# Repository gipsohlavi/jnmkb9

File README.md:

サリチル酸（https://salicylic-acid3.hatenablog.com/about）  氏の著作「自作キーボード設計ガイド」をもとに作成した、<br>完全自作９キーキーボードです。

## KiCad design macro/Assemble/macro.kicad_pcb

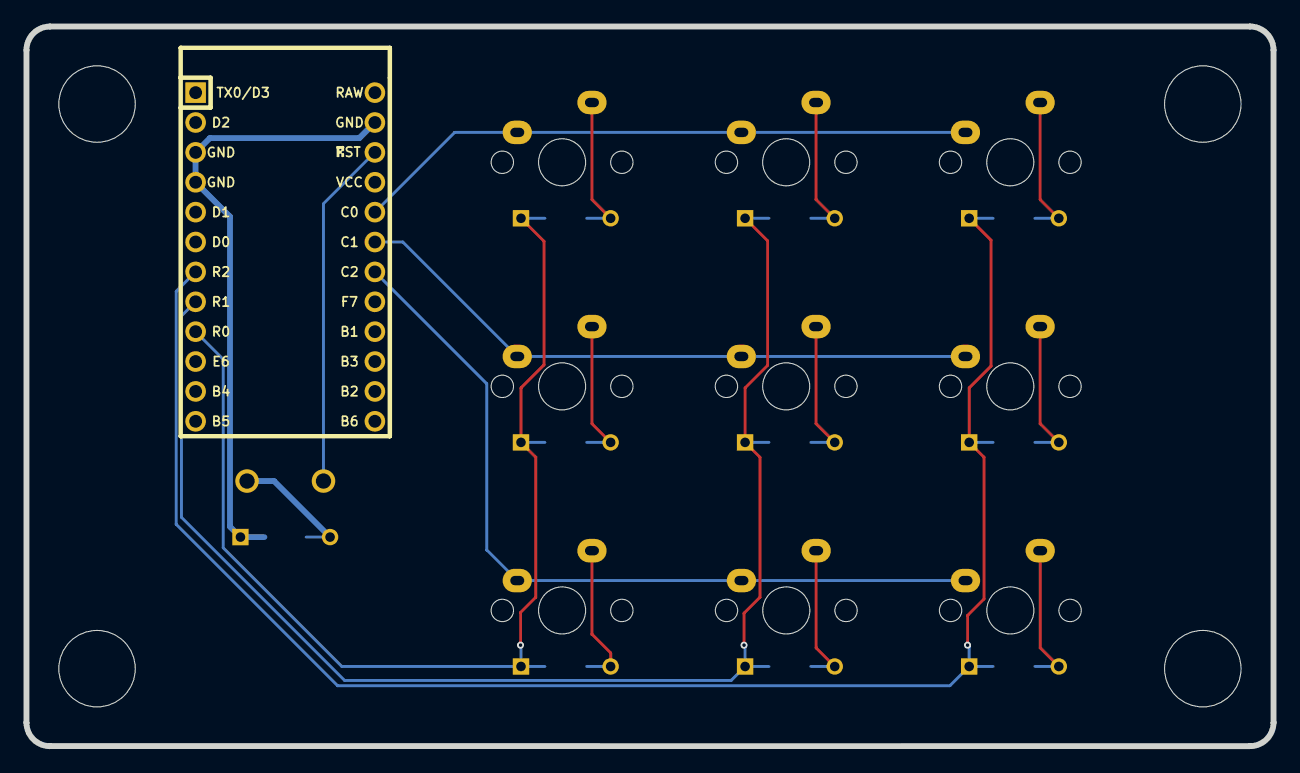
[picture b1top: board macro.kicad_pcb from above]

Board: 2 copper layers, 106.0 x 61.2 mm, 25 parts (0 on the bottom side), 18 nets.

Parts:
D1, D2, D3, D4, D5, D6, D7, D8, D9, D10: D; Diode_TH_SMD
Ref**: Val**; m3_Spacer_Hole
Ref**#2, Ref**#3, Ref**#4: Val**; m3_Spacer_Hole
SW1, SW2, SW3, SW4, SW5, SW6, SW7, SW8, SW9: SW_Push; CherryMX_Solder_1u
SW10: SW_Push; ResetSW
U1: ProMicro; ArduinoProMicro

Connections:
Col0: SW1.1, SW4.1, SW7.1, U1.20 (F4/A3)
Col1: SW2.1, SW5.1, SW8.1, U1.19 (F5/A2)
Col2: SW3.1, SW6.1, SW9.1, U1.18 (F6/A1)
GND: D10.1 (K), U1.3 (GND), U1.4 (GND), U1.23 (GND)
unnamed: D1.2 (A), SW1.2
unnamed: D2.2 (A), SW2.2
unnamed: D3.2 (A), SW3.2
unnamed: D4.2 (A), SW4.2
unnamed: D5.2 (A), SW5.2
unnamed: D6.2 (A), SW6.2
unnamed: D7.2 (A), SW7.2
unnamed: D8.2 (A), SW8.2
unnamed: D9.2 (A), SW9.2
unnamed: D10.2 (A), SW10.2
Reset: SW10.1, U1.22 (RST)
Row0: D1.1 (K), D2.1 (K), D3.1 (K), U1.9 (6/D7)
Row1: D4.1 (K), D5.1 (K), D6.1 (K), U1.8 (5/C6)
Row2: D7.1 (K), D8.1 (K), D9.1 (K), U1.7 (4/D4)

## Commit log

2025-08-17 no message
